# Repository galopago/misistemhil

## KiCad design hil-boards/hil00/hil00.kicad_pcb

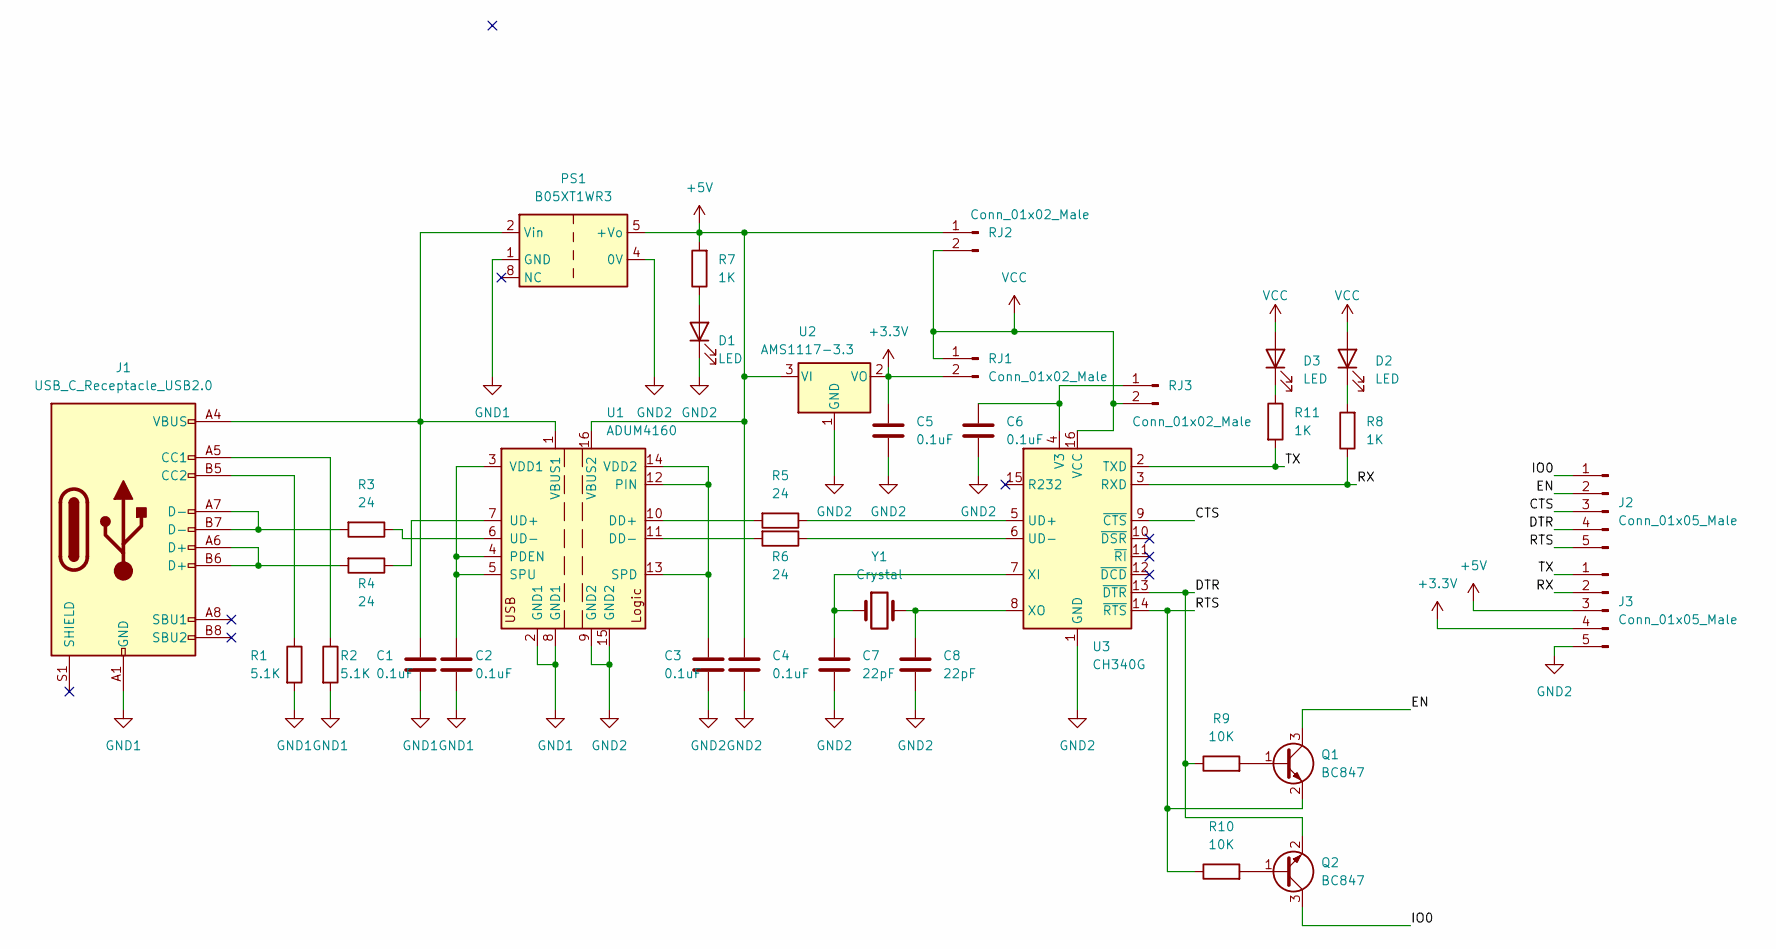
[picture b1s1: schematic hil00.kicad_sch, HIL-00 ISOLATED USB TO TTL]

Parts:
C1, C2, C3, C4, C5, C6: 0.1uF; C_0805_2012Metric_Pad1.18x1.45mm_HandSolder
C7, C8: 22pF; C_0805_2012Metric_Pad1.18x1.45mm_HandSolder
D1, D2, D3: LED; D_0805_2012Metric_Pad1.15x1.40mm_HandSolder
J1: USB_C_Receptacle_USB2.0; USB_C_Receptacle_HRO_TYPE-C-31-M-12
J2, J3: Conn_01x05_Male; TerminalBlock_4Ucon_1x05_P3.50mm_Horizontal
PS1: B05XT1WR3; Converter_DCDC_Mornsun_B05_XT_1WR3_SMD
Q1, Q2: BC847; SOT-23
R1, R2: 5.1K; R_0805_2012Metric_Pad1.20x1.40mm_HandSolder
R3, R4, R5, R6: 24; R_0805_2012Metric_Pad1.20x1.40mm_HandSolder
R7, R8, R11: 1K; R_0805_2012Metric_Pad1.20x1.40mm_HandSolder
R9, R10: 10K; R_0805_2012Metric_Pad1.20x1.40mm_HandSolder
RJ1, RJ2, RJ3: Conn_01x02_Male; PinHeader_1x02_P2.54mm_Vertical
U1: ADUM4160; SOIC-16W_7.5x10.3mm_P1.27mm
U2: AMS1117-3.3; SOT-223-3_TabPin2
U3: CH340G; SOIC-16_3.9x9.9mm_P1.27mm
Y1: Crystal; Crystal_SMD_HC49-SD_HandSoldering_Compact

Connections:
+3.3V: C5.1, J3.4, RJ1.2, U2.2 (VO)
+5V: C4.1, J3.3, PS1.5 (+Vo), R7.2, RJ2.1, U1.16 (VBUS2), U2.3 (VI)
/CTS: J2.3, U3.9 (~CTS)
/DTR: J2.4, Q2.2 (E), R9.1, U3.13 (~DTR)
/EN: J2.2, Q1.3 (C)
/IO0: J2.1, Q2.3 (C)
/RTS: J2.5, Q1.2 (E), R10.1, U3.14 (~RTS)
/RX: J3.2, R8.1, U3.3 (RXD)
/TX: J3.1, R11.2, U3.2 (TXD)
GND1: C1.2, C2.2, J1.A1 (GND), J1.A12 (GND), J1.B1 (GND), J1.B12 (GND), PS1.1 (GND), R1.2, R2.2, U1.2 (GND1), U1.8 (GND1)
GND2: C3.2, C4.2, C5.2, C6.2, C7.2, C8.2, D1.1 (K), J3.5, PS1.4 (0V), U1.9 (GND2), U1.15 (GND2), U2.1 (GND), U3.1 (GND)
unnamed: C1.1, J1.A4 (VBUS), J1.A9 (VBUS), J1.B4 (VBUS), J1.B9 (VBUS), PS1.2 (Vin), U1.1 (VBUS1)
unnamed: C2.1, U1.3 (VDD1), U1.4 (PDEN), U1.5 (SPU)
unnamed: C3.1, U1.12 (PIN), U1.13 (SPD), U1.14 (VDD2)
unnamed: C6.1, RJ3.1, U3.4 (V3)
unnamed: C7.1, U3.7 (XI), Y1.1
unnamed: C8.1, U3.8 (XO), Y1.2
unnamed: D1.2 (A), R7.1
unnamed: D2.1 (K), R8.2
unnamed: D3.1 (K), R11.1
unnamed: J1.A5 (CC1), R2.1
unnamed: J1.A6 (D+), J1.B6 (D+), R4.2
unnamed: J1.A7 (D-), J1.B7 (D-), R3.2
unnamed: J1.B5 (CC2), R1.1
unnamed: Q1.1 (B), R9.2
unnamed: Q2.1 (B), R10.2
unnamed: R3.1, U1.6 (UD-)
unnamed: R4.1, U1.7 (UD+)
unnamed: R5.1, U3.5 (UD+)
unnamed: R5.2, U1.10 (DD+)
unnamed: R6.1, U3.6 (UD-)
unnamed: R6.2, U1.11 (DD-)
VCC: D2.2 (A), D3.2 (A), RJ1.1, RJ2.2, RJ3.2, U3.16 (VCC)

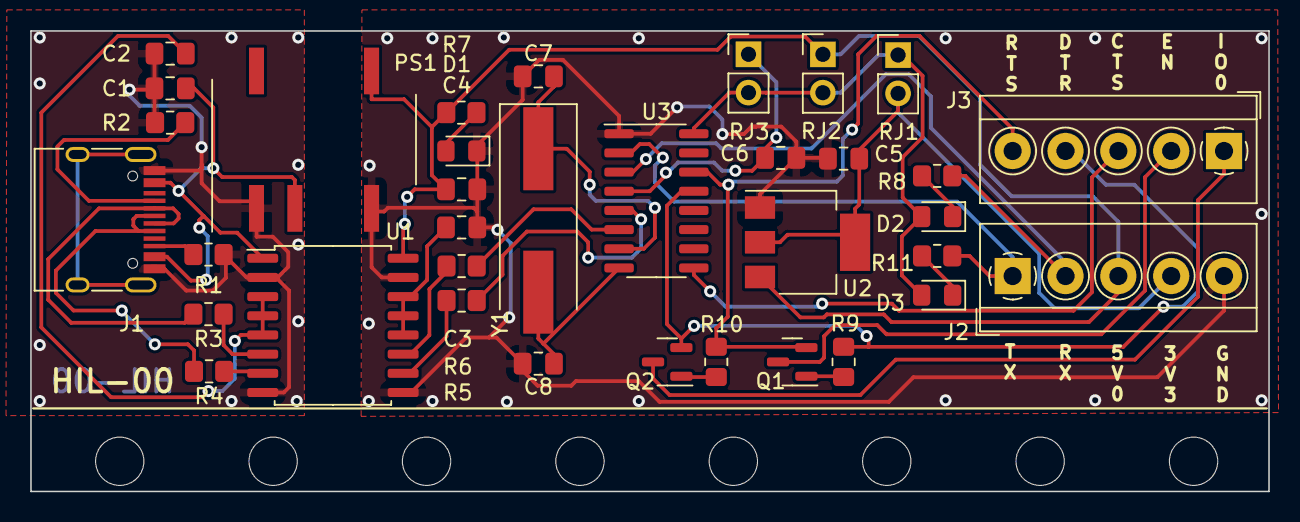
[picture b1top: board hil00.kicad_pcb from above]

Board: 2 copper layers, 82.0 x 30.5 mm, 35 parts (0 on the bottom side), 33 nets.
